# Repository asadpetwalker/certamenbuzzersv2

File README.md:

# CertamenBuzzersV2

A buzzer system for the game Certamen about Roman language, mythology, history, and culture. It is a quiz bowl style game, where whoever buzzes first gets a chance to claim the points.

# Why I made this

I made this because right now buzzer systems are inaccessible. Buzzer systems are sold by JCL, but they have a monopoly over it, so they mark up the prices incredibly even though the electronics are fairly simple, to 800 dollars. for the small version. I made this for my team, because they need a buzzer system to get practice in, since hyperbuzzing is an important strategy in more competitive leagues, as well as the fact that the current version is very bulky and you cannot bring it to places for practice.

# Wiring Diagram

Wire - Button - Wire

# Pictures

# BOM

| Name | Purpose | Quantity | Total Cost (USD) | Link | Distributor |
|------|---------|----------|------------------|------|--------------|
| Soldering Iron | Soldering | 1 | 34.96 | [Amazon](https://www.amazon.com/Soldering-Temperature-200-480%E2%84%83-Compatible-Function/dp/B0FJDRF6S5/ref=sr_1_4?sr=8-4) | Amazon |
| 6P4C RJ11 Connector | Connecting to wires | 1 | 5.89 | [Amazon](https://www.amazon.com/Telephone-Modular-Connector-Compatible-Stranded/dp/B07YZ79DCY/ref=sr_1_3?sr=8-3) | Amazon |
| Buttons | Buttoning | 1 | 7.99 | [Amazon](https://www.amazon.com/Twidec-Momentary-Button-Pre-soldered-R13-507BK-X/dp/B0CYSSFWSS/ref=pd_ci_mcx_di_int_sccai_cn_d_sccl_1_2/137-6738652-1809662) | Amazon |
| PCB + Stencil | PCB | 1 | 6.15 | | JLCPCB |
| 4 | RF TXRX MODULE BT PCB TRACE SMD | 2 | 10.42 | | Digikey |
| 3 | IC REG LINEAR 3.3V 1A SOT-223 | 2 | 0.76 | | Digikey |
| 2 | SWITCH TACTILE SPST-NO 0.05A 32V | 4 | 2.68 | | Digikey |
| 1 | RES 10K OHM 1% 1/10W 0603 | 50 | 0.75 | | Digikey |

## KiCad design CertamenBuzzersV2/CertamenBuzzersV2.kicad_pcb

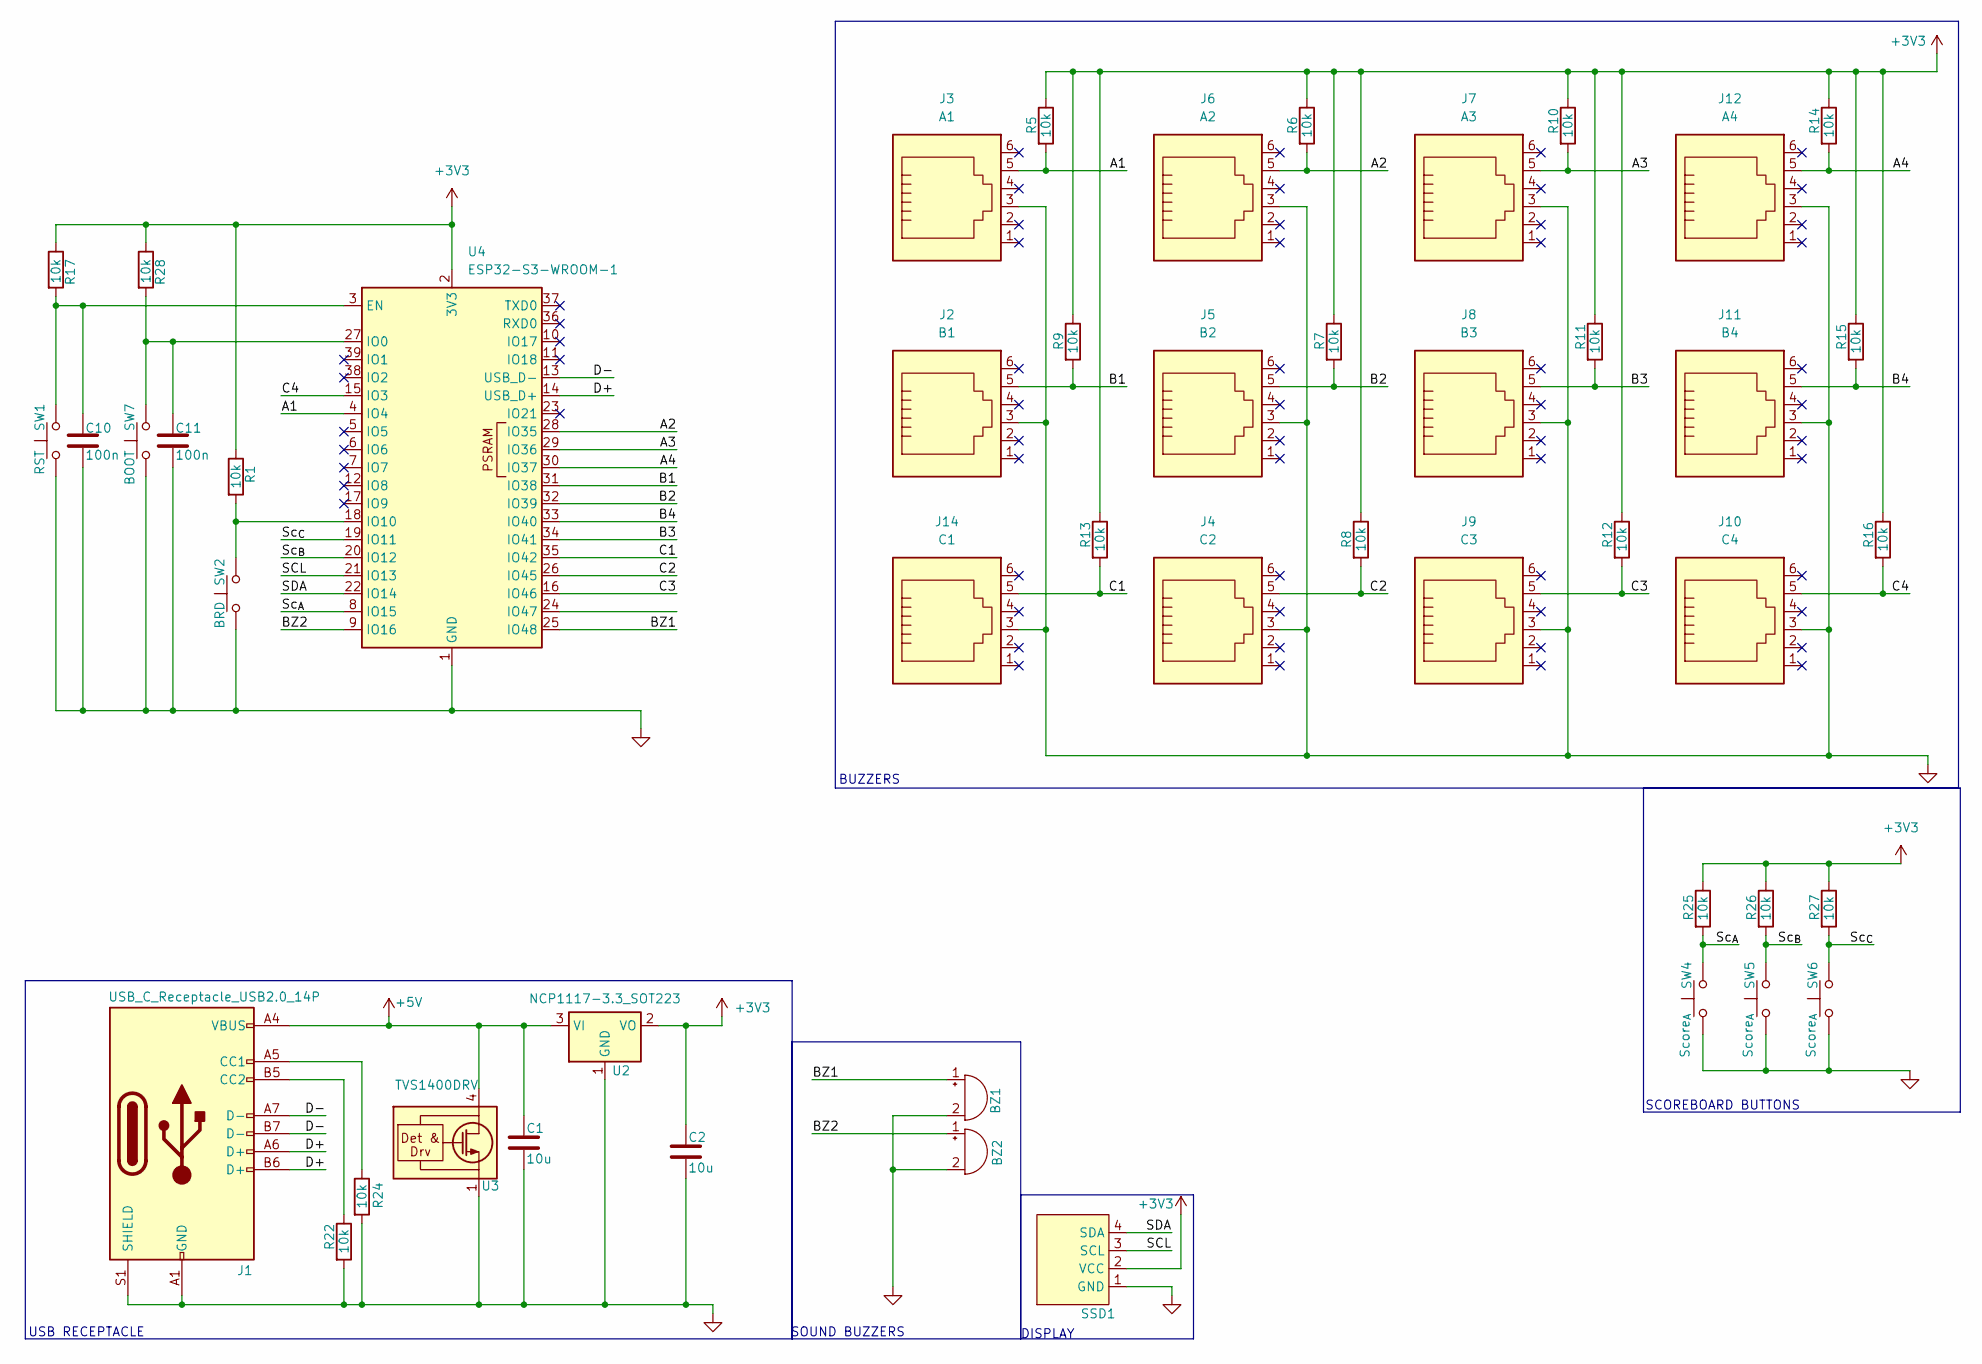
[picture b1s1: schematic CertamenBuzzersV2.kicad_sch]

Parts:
BZ1, BZ2: Buzzer; Buzzer_TDK_PS1240P02BT_D12.2mm_H6.5mm
C1, C2: 10u; C_0805_2012Metric
C10, C11: 100n; C_0805_2012Metric
J1: USB_C_Receptacle_USB2.0_14P; USB_C_Receptacle_GCT_USB4105-xx-A_16P_TopMnt_Horizontal
J2: B1; RJ25_Wayconn_MJEA-660X1_Horizontal
J3: A1; RJ25_Wayconn_MJEA-660X1_Horizontal
J4: C2; RJ25_Wayconn_MJEA-660X1_Horizontal
J5: B2; RJ25_Wayconn_MJEA-660X1_Horizontal
J6: A2; RJ25_Wayconn_MJEA-660X1_Horizontal
J7: A3; RJ25_Wayconn_MJEA-660X1_Horizontal
J8: B3; RJ25_Wayconn_MJEA-660X1_Horizontal
J9: C3; RJ25_Wayconn_MJEA-660X1_Horizontal
J10: C4; RJ25_Wayconn_MJEA-660X1_Horizontal
J11: B4; RJ25_Wayconn_MJEA-660X1_Horizontal
J12: A4; RJ25_Wayconn_MJEA-660X1_Horizontal
J14: C1; RJ25_Wayconn_MJEA-660X1_Horizontal
R1, R5, R6, R7, R8, R9, R10, R11, R12, R13, R14, R15, R16, R17, R22, R24, R25, R26, R27, R28: 10k; R_0603_1608Metric
SSD1: PinSocket_1x04_P2.54mm_Vertical
SW1: RST; SW_Push_1P1T_NO_CK_KMR2
SW2: BRD; PinSocket_1x02_P2.54mm_Vertical
SW4, SW5, SW6: Score_{A}; PinSocket_1x02_P2.54mm_Vertical
SW7: BOOT; SW_Push_1P1T_NO_CK_KMR2
U2: NCP1117-3.3_SOT223; SOT-223-3_TabPin2
U3: TVS1400DRV; WSON-6-1EP_2x2mm_P0.65mm_EP1x1.6mm
U4: ESP32-S3-WROOM-1

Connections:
+3V3: C2.1, R1.1, R5.1, R6.1, R7.1, R8.1, R9.1, R10.1, R11.1, R12.1, R13.1, R14.1, R15.1, R16.1, R17.1, R25.1, R26.1, R27.1, R28.1, SSD1.2 (VCC), U2.2 (VO), U4.2 (3V3)
+5V: C1.1, J1.A4 (VBUS), J1.A9 (VBUS), J1.B4 (VBUS), J1.B9 (VBUS), U2.3 (VI), U3.4 (IN), U3.5 (IN), U3.6 (IN)
/A1: J3.5, R5.2, U4.4 (IO4)
/A2: J6.5, R6.2, U4.28 (IO35)
/A3: J7.5, R10.2, U4.29 (IO36)
/A4: J12.5, R14.2, U4.30 (IO37)
/B1: J2.5, R9.2, U4.31 (IO38)
/B2: J5.5, R7.2, U4.32 (IO39)
/B3: J8.5, R11.2, U4.34 (IO41)
/B4: J11.5, R15.2, U4.33 (IO40)
/BZ1: BZ1.1 (+), U4.25 (IO48)
/BZ2: BZ2.1 (+), U4.9 (IO16)
/C1: J14.5, R13.2, U4.35 (IO42)
/C2: J4.5, R8.2, U4.26 (IO45)
/C3: J9.5, R12.2, U4.16 (IO46)
/C4: J10.5, R16.2, U4.15 (IO3)
/D+: J1.A6 (D+), J1.B6 (D+), U4.14 (USB_D+)
/D-: J1.A7 (D-), J1.B7 (D-), U4.13 (USB_D-)
/SCL: SSD1.3 (SCL), U4.21 (IO13)
/SDA: SSD1.4 (SDA), U4.22 (IO14)
/Sc_{A}: R25.2, SW4.2, U4.8 (IO15)
/Sc_{B}: R26.2, SW5.2, U4.20 (IO12)
/Sc_{C}: R27.2, SW6.2, U4.19 (IO11)
GND: BZ1.2 (-), BZ2.2 (-), C1.2, C2.2, C10.2, C11.2, J1.A1 (GND), J1.A12 (GND), J1.B1 (GND), J1.B12 (GND), J1.S1 (SHIELD), J2.3, J3.3, J4.3, J5.3, J6.3, J7.3, J8.3, J9.3, J10.3, J11.3, J12.3, J14.3, R22.2, R24.2, SSD1.1 (GND), SW1.1, SW2.1, SW4.1, SW5.1, SW6.1, SW7.1, U2.1 (GND), U3.1 (GND), U3.2 (GND), U3.3 (GND), U3.7 (GND), U4.1 (GND), U4.40 (GND), U4.41 (GND)
unnamed: J1.A5 (CC1), R24.1
unnamed: J1.B5 (CC2), R22.1
unnamed: C10.1, R17.2, SW1.2, U4.3 (EN)
unnamed: C11.1, R28.2, SW7.2, U4.27 (IO0)
unnamed: R1.2, SW2.2, U4.18 (IO10)

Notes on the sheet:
SOUND BUZZERS
DISPLAY
BUZZERS
USB RECEPTACLE
SCOREBOARD BUTTONS

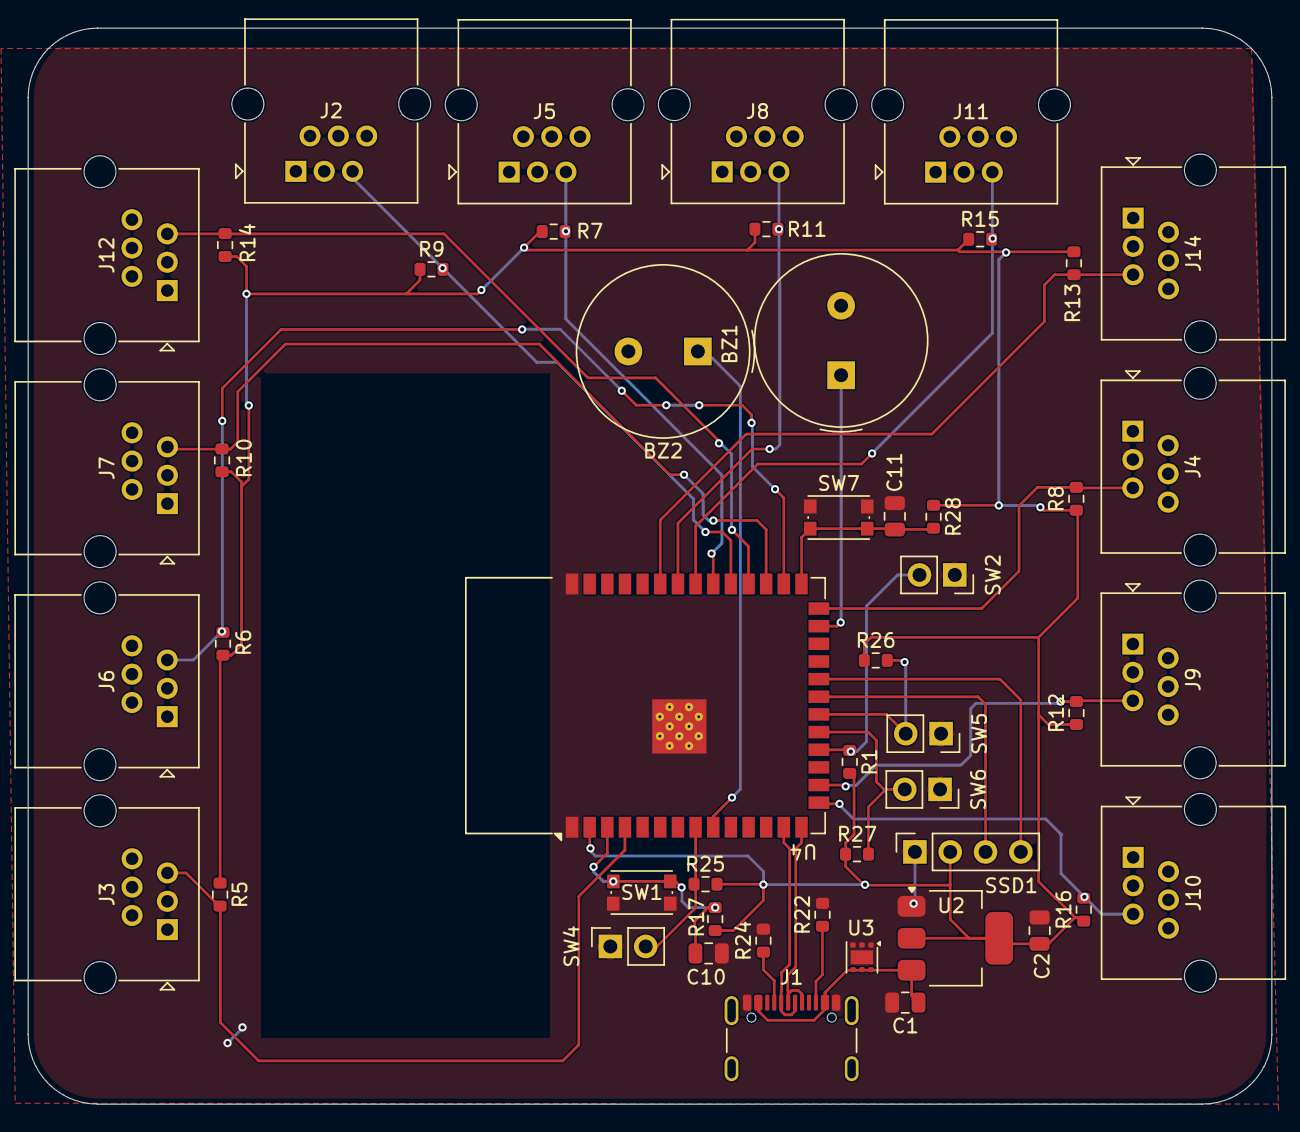
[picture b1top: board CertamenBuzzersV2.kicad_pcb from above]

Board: 2 copper layers, 89.5 x 77.4 mm, 49 parts (0 on the bottom side), 29 nets.

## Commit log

2026-06-11 all the stuff
2026-06-11 build pic
2026-06-11 build pic readme
